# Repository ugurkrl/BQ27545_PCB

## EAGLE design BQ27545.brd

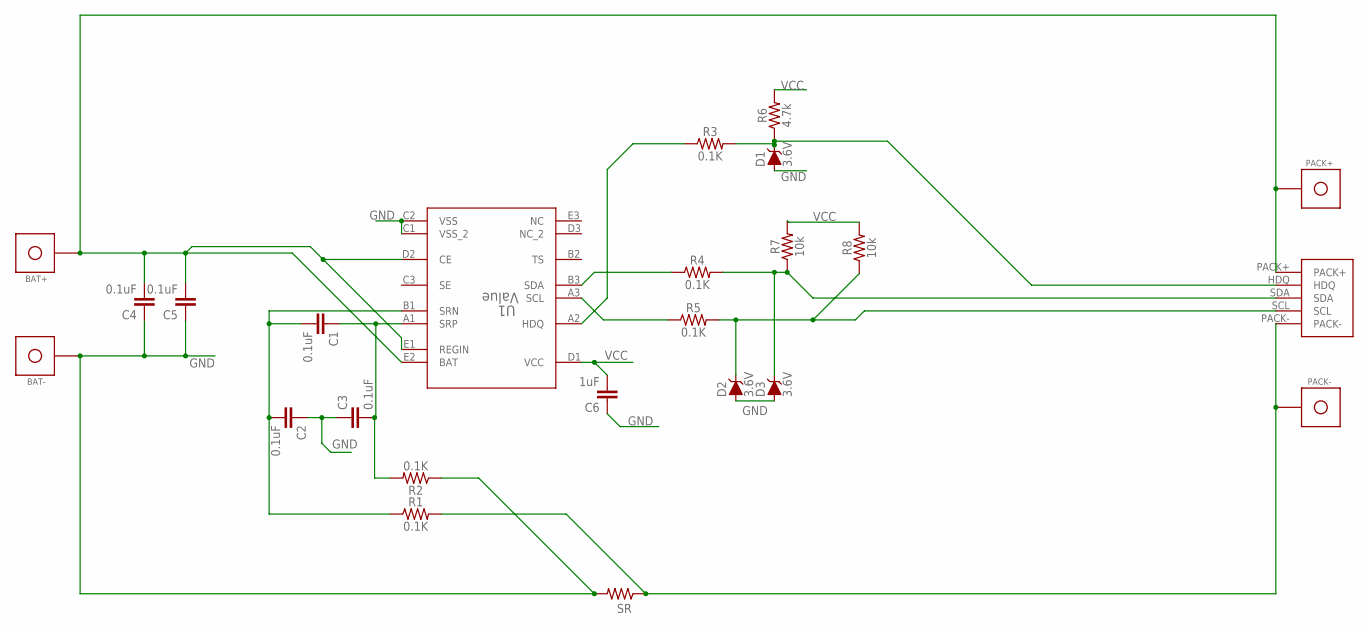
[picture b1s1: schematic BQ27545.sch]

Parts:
BAT+: BAT_TAB; BATT_TAB
BAT-: BAT_TAB; BATT_TAB
C1, C2, C3, C4, C5: 0.1uF; 0402
C6: 1uF; 0402
D1, D2, D3: 3.6V; SOD-323
PACK+: BAT_TAB; BATT_TAB
PACK-: BAT_TAB; BATT_TAB
R1, R2, R3, R4, R5: 0.1K; 0402
R6: 4.7k; 0402
R7, R8: 10k; 0402
SR: R-US_R2512; R2512
U1: Value; YZF0015BBBP
U$1: BAT_COMM_PWR_REV; BATT_COMM_PWR_REV

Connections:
GND: BAT-.P$1, C2.1, C3.1, C4.1, C5.1, C6.1, D1.A, D2.A, D3.A, R2.1, SR.2, U1.C1 (VSS_2), U1.C2 (VSS)
unnamed: R3.1, U1.A2 (HDQ)
unnamed: PACK-.P$1, R1.2, SR.1, U$1.PACK-
unnamed: C1.1, C3.2, R2.2, U1.A1 (SRP)
unnamed: C1.2, C2.2, R1.1, U1.B1 (SRN)
unnamed: D1.C, R3.2, R6.1, U$1.HDQ
unnamed: R4.1, U1.B3 (SDA)
unnamed: R5.1, U1.A3 (SCL)
unnamed: D3.C, R4.2, R7.1, U$1.SDA
unnamed: D2.C, R5.2, R8.1, U$1.SCL
PACK+: BAT+.P$1, C4.2, C5.2, PACK+.P$1, U1.D2 (CE), U1.E1 (REGIN), U1.E2 (BAT), U$1.PACK+
VCC: C6.2, R6.2, R7.2, R8.2, U1.D1 (VCC)

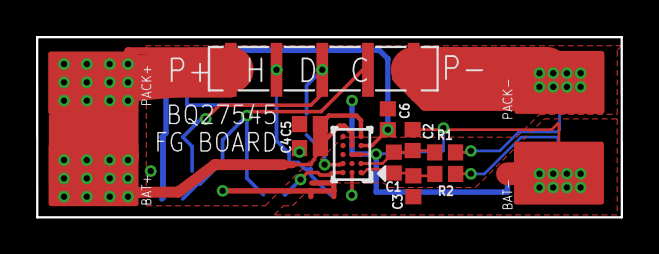
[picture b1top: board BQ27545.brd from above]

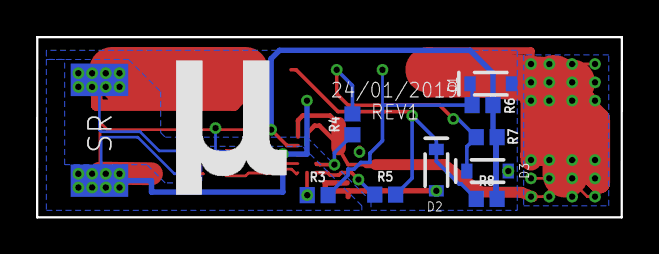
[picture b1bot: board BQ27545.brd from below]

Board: 2 copper layers, 32.5 x 10.0 mm, 24 parts (10 on the bottom side), 12 nets.

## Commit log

2019-01-27 Add gerber files (exported using elecrow cam job)
2019-01-27 added oshpark gerber pictures
2019-01-27 change variables

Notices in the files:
parts and their libraries:
SparkFun-Resistors: Licensing: Creative Commons ShareAlike 4.0 International - https://creativecommons.org/licenses/by-sa/4.0
